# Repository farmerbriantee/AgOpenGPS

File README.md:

# AgOpenGPS - Guidance software

Ag Precision Mapping and Section Control Software

AgOpenGPS is 2 programs. AgIO is the communication hub to the outside world and AgOpenGPS is the 
application. You can run either and within each, you can run the other.

You only need to run AgOpenGPS if you are using the simulator.

The software reads NMEA strings for the purpose of recording and mapping position information 
for Agricultural use. Also it has up to 16 sections of Section Control that can have unique widths 
or up to 64 same width sections to control implements application of product preventing 
over-application.

Also ouputs Pure pursuit steer angles from reference line for AB line, AB Curve and Contour guidance. 
Auto Headland called UTurn on Curve and AB Line with loops for narrow equipment. 
Mapping as a background can also be added.

Included in this repository is an application, and source folders. 

See the PCB repo for PCB layouts, firmware for steering and rate control, machine control, GPS and simulator. 

## Installation

1. Download the [Most Stable AgOpenGPS Release](https://github.com/farmerbriantee/AgOpenGPS/releases)
2. Unzip or extract the contents to a folder (folder accessible by user not the root of C:\\)
Even on your desktop
3. Run AgOpenGPS.exe

## Links

- [AgOpenGPS Wiki](https://github.com/farmerbriantee/AgOpenGPS/wiki)
- [AgOpenGPS Forum](https://discourse.agopengps.com/)
- [PCB and Firmware Repository](https://github.com/AgHardware/Boards)
- [SK21 Rate Control Repository](https://github.com/AgHardware/Rate_Control)
- [AgHardware Wiki](https://github.com/AgHardware/Boards/wiki)

## License

If you distribute copies of such a program, whether
gratis or for a fee, you must pass on to the recipients the same
freedoms that you received.  You must make sure that they, too, receive
or can get the source code.  And you must show them these terms so they
know their rights as Outlined in the GPLv3 License.

THIS SOFTWARE IS PROVIDED BY THE COPYRIGHT HOLDERS AND CONTRIBUTORS "AS IS" AND ANY EXPRESS OR IMPLIED WARRANTIES, INCLUDING, BUT NOT LIMITED TO, THE IMPLIED WARRANTIES OF MERCHANTABILITY AND FITNESS FOR A PARTICULAR PURPOSE ARE DISCLAIMED.
IN NO EVENT SHALL <COPYRIGHT HOLDER> BE LIABLE FOR ANY DIRECT, INDIRECT, INCIDENTAL, SPECIAL, EXEMPLARY, OR CONSEQUENTIAL DAMAGES (INCLUDING, BUT NOT LIMITED TO, PROCUREMENT OF SUBSTITUTE GOODS OR SERVICES;
LOSS OF USE, DATA, OR PROFITS; OR BUSINESS INTERRUPTION) HOWEVER CAUSED AND ON ANY THEORY OF LIABILITY, WHETHER IN CONTRACT, STRICT LIABILITY, OR TORT (INCLUDING NEGLIGENCE OR OTHERWISE) ARISING IN ANY WAY OUT OF THE USE OF THIS SOFTWARE, EVEN IF ADVISED OF THE POSSIBILITY OF SUCH DAMAGE.

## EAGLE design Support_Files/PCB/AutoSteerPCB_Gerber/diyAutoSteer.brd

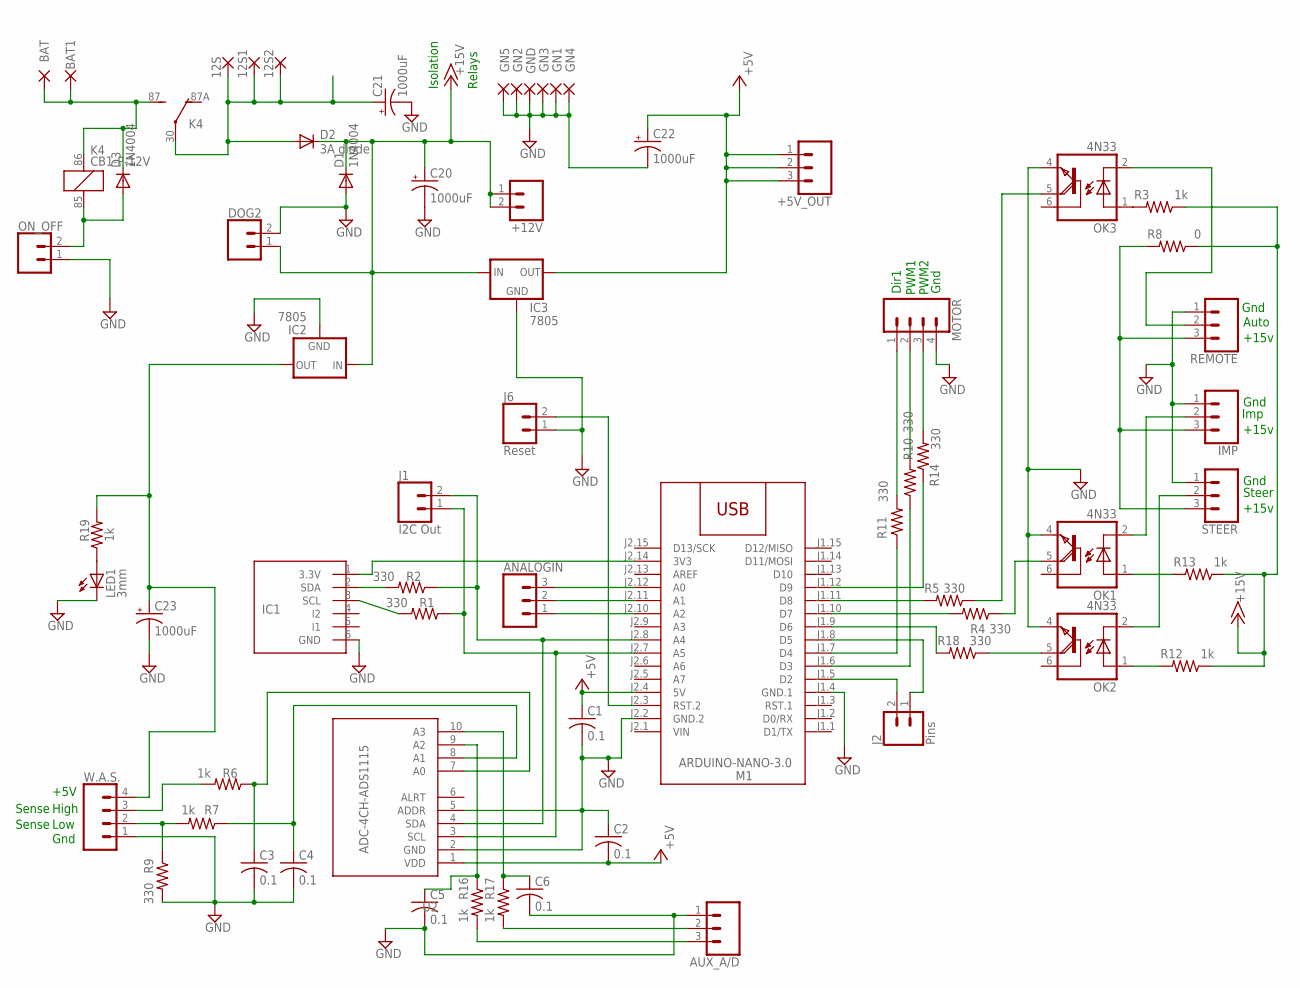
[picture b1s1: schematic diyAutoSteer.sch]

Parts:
12S, 12S1, 12S2: WIREPAD3,81/1,1; 3,81/1,1
+5V_OUT: CONN_03LONGPADS; 1X03_LONGPADS
+12V: CONN_02PTH3; 1X02_LONGPADS
ANALOGIN: CONN_03LONGPADS; 1X03_LONGPADS
AUX_A/D: CONN_03LONGPADS; 1X03_LONGPADS
BAT, BAT1: WIREPAD3,81/1,1; 3,81/1,1
C1, C2, C3, C4, C5, C6: 0.1; C025-025X050
C20, C21, C22, C23: 1000uF; E5-10,5
D1, D3: 1N4004; DO41-10
D2: 3A diode; DO27-15
DOG2: CONN_02PTH3; 1X02_LONGPADS
GN1, GN2, GN3, GN4, GN5: WIREPAD3,81/1,1; 3,81/1,1
GND: WIREPAD3,81/1,1; 3,81/1,1
IC1: MMA8452Q; BREAKOUT_6PIN
IC2, IC3: 7805; 78XXS
IMP: CONN_03LONGPADS; 1X03_LONGPADS
J1: I2C Out; 1X02_LONGPADS
J2: Pins; 1X02_LONGPADS
J6: Reset; 1X02_LONGPADS
K4: CB1-P-12V; CB1
LED1: 3mm; LED3MM
M1: ARDUINO-NANO-3.0
MOTOR: CONN_04LONGPADS; 1X04_LONGPADS
OK1, OK2, OK3: 4N33; DIL06
ON_OFF: CONN_02PTH3; 1X02_LONGPADS
R1, R2, R4, R5, R9, R10, R11, R14, R18: 330; 0309/12
R3, R6, R7, R12, R13, R16, R17, R19: 1k; 0309/12
R8: 0; 0309/12
REMOTE: CONN_03LONGPADS; 1X03_LONGPADS
STEER: CONN_03LONGPADS; 1X03_LONGPADS
U2: ADC-4CH-ADS1115
W.A.S.: CONN_04LONGPADS; 1X04_LONGPADS

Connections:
+5V: +5V_OUT.1, +5V_OUT.2, +5V_OUT.3, C1.1, C2.2, C22.+, IC3.OUT, M1.J2.4 (5V), U2.1 (VDD)
+15V: +12V.1, +12V.2, C20.+, D1.C, D2.C, DOG2.1, IC2.IN, IC3.IN, R3.1, R8.1, R12.1, R13.1
BATT: BAT.1, BAT1.1, D3.C, K4.86 (1), K4.87 (S)
GND: AUX_A/D.1, C1.2, C2.1, C3.2, C4.2, C5.2, C6.2, C20.-, C21.-, C22.-, C23.-, D1.A, DOG2.2, GN1.1, GN2.1, GN3.1, GN4.1, GN5.1, GND.1, IC1.6 (GND), IC2.GND, IC3.GND, IMP.1, J6.1, LED1.K (C), M1.J1.4 (GND.1), M1.J2.2 (GND.2), MOTOR.4, OK1.4 (E), OK2.4 (E), OK3.4 (E), ON_OFF.1, R9.2, REMOTE.1, STEER.1, U2.2 (GND), U2.5 (ADDR), W.A.S..1
unnamed: IC1.1 (3.3V), M1.J2.14 (3V3)
unnamed: R7.2, R9.1, W.A.S..2
unnamed: IMP.3, R8.2, REMOTE.3, STEER.3
unnamed: M1.J1.6 (D3), R10.1
unnamed: M1.J1.7 (D4), R11.1
unnamed: J2.2, M1.J1.5 (D2)
unnamed: J6.2, M1.J2.3 (RST.2)
unnamed: R6.2, W.A.S..3
unnamed: ANALOGIN.3, M1.J2.12 (A0)
unnamed: M1.J1.12 (D9), R14.1
unnamed: IC1.2 (SDA), R2.2
unnamed: IC1.3 (SCL), R1.2
unnamed: ANALOGIN.2, M1.J2.11 (A1)
unnamed: ANALOGIN.1, M1.J2.10 (A2)
unnamed: LED1.A, R19.1
unnamed: MOTOR.2, R10.2
unnamed: J2.1, M1.J1.8 (D5)
unnamed: MOTOR.1, R11.2
unnamed: C3.1, R6.1, U2.7 (A0)
unnamed: MOTOR.3, R14.2
unnamed: OK2.2 (C), STEER.2
unnamed: M1.J1.11 (D8), R5.2
unnamed: D3.A, K4.85 (2), ON_OFF.2
unnamed: OK2.1 (A), R12.2
unnamed: OK3.1 (A), R3.2
unnamed: M1.J1.10 (D7), R4.2
unnamed: OK3.2 (C), REMOTE.2
unnamed: IMP.2, OK1.2 (C)
unnamed: M1.J1.9 (D6), R18.2
unnamed: OK1.1 (A), R13.2
unnamed: OK3.5 (COL), R5.1
unnamed: C6.1, R17.1, U2.10 (A3)
unnamed: C5.1, R16.1, U2.9 (A2)
unnamed: OK1.5 (COL), R4.1
unnamed: AUX_A/D.2, R17.2
unnamed: OK2.5 (COL), R18.1
unnamed: C4.1, R7.1, U2.8 (A1)
unnamed: AUX_A/D.3, R16.2
SCL: J1.1, M1.J2.7 (A5), R1.1, U2.3 (SCL)
SDA: J1.2, M1.J2.8 (A4), R2.1, U2.4 (SDA)
SW_RAW: 12S.1, 12S1.1, 12S2.1, C21.+, D2.A, K4.30
V+WAS: C23.+, IC2.OUT, R19.2, W.A.S..4
VIN: M1.J2.1 (VIN)

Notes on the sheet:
Gnd
Low
High
+5V
PWM1
PWM2
Dir1
Steer
Imp
Sense
Auto
Isolation
Relays
+15v

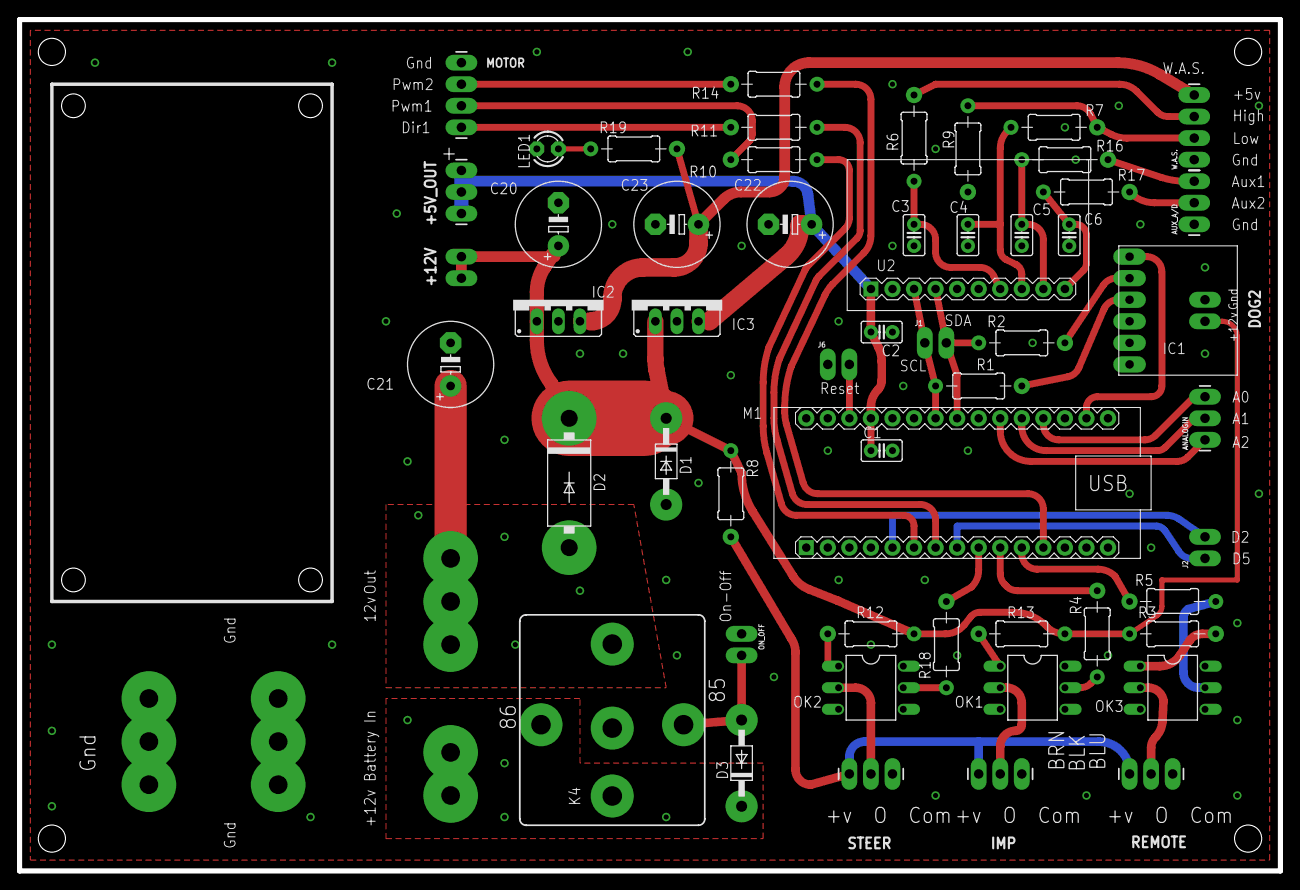
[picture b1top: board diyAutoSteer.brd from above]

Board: 2 copper layers, 148.6 x 100.3 mm, 66 parts (0 on the bottom side), 46 nets.

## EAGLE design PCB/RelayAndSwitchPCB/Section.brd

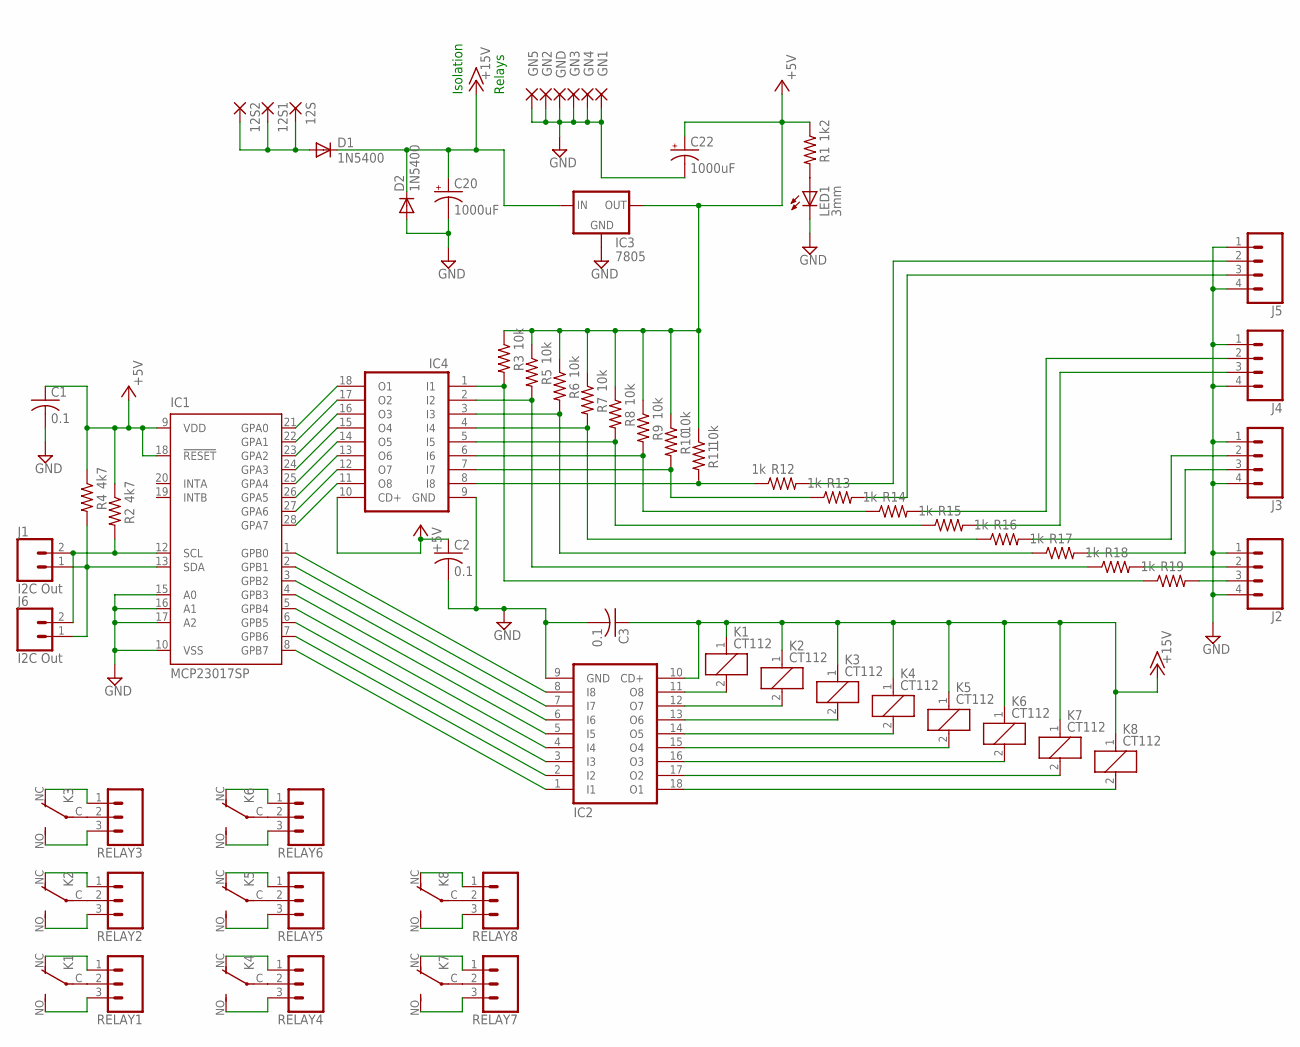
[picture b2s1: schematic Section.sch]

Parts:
12S, 12S1, 12S2: WIREPAD3,81/1,1; 3,81/1,1
C1, C2, C3: 0.1; C025-025X050
C20, C22: 1000uF; E5-10,5
D1, D2: 1N5400; DO201-15
GN1, GN2, GN3, GN4, GN5: WIREPAD3,81/1,1; 3,81/1,1
GND: WIREPAD3,81/1,1; 3,81/1,1
IC1: MCP23017SP; DIL28-3
IC2, IC4: ULN2803A; DIL18
IC3: 7805; 78XXS
J1, J6: I2C Out; 1X02_LONGPADS
J2, J3, J4, J5: CONN_04LONGPADS; 1X04_LONGPADS
K1, K2, K3, K4, K5, K6, K7, K8: CT112; CT-SLIM
LED1: 3mm; LED3MM
R1: 1k2; 0309/12
R2, R4: 4k7; 0309/12
R3, R5, R6, R7, R8, R9, R10, R11: 10k; 0309/12
R12, R13, R14, R15, R16, R17, R18, R19: 1k; 0309/12
RELAY1, RELAY2, RELAY3, RELAY4, RELAY5, RELAY6, RELAY7, RELAY8: CONN_03LONGPADS; 1X03_LONGPADS

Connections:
+5V: C1.1, C2.1, C22.+, IC1.9 (VDD), IC1.18 (!RESET), IC3.OUT, IC4.10 (CD+), R1.1, R2.1, R3.1, R4.1, R5.1, R6.1, R7.1, R8.1, R9.1, R10.1, R11.1
+12SW: 12S.1, 12S1.1, 12S2.1, D1.A
+15V: C3.1, C20.+, D1.C, D2.C, IC2.10 (CD+), IC3.IN, K1.1, K2.1, K3.1, K4.1, K5.1, K6.1, K7.1, K8.1
GND: C1.2, C2.2, C3.2, C20.-, C22.-, D2.A, GN1.1, GN2.1, GN3.1, GN4.1, GN5.1, GND.1, IC1.10 (VSS), IC1.15 (A0), IC1.16 (A1), IC1.17 (A2), IC2.9 (GND), IC3.GND, IC4.9 (GND), J2.1, J2.4, J3.1, J3.4, J4.1, J4.4, J5.1, J5.4, LED1.K (C)
unnamed: IC2.11 (O8), K1.2
unnamed: IC1.1 (GPB0), IC2.8 (I8)
unnamed: IC1.2 (GPB1), IC2.7 (I7)
unnamed: IC1.3 (GPB2), IC2.6 (I6)
unnamed: IC1.4 (GPB3), IC2.5 (I5)
unnamed: IC1.5 (GPB4), IC2.4 (I4)
unnamed: IC1.6 (GPB5), IC2.3 (I3)
unnamed: IC1.7 (GPB6), IC2.2 (I2)
unnamed: IC1.8 (GPB7), IC2.1 (I1)
unnamed: IC2.12 (O7), K2.2
unnamed: IC2.13 (O6), K3.2
unnamed: IC2.14 (O5), K4.2
unnamed: IC2.15 (O4), K5.2
unnamed: IC2.16 (O3), K6.2
unnamed: IC2.17 (O2), K7.2
unnamed: IC2.18 (O1), K8.2
unnamed: IC1.21 (GPA0), IC4.18 (O1)
unnamed: IC1.22 (GPA1), IC4.17 (O2)
unnamed: K1.C, RELAY1.2
unnamed: K2.C, RELAY2.2
unnamed: K3.C, RELAY3.2
unnamed: K5.C, RELAY5.2
unnamed: K4.C, RELAY4.2
unnamed: K6.C, RELAY6.2
unnamed: K7.C, RELAY7.2
unnamed: IC1.23 (GPA2), IC4.16 (O3)
unnamed: K8.C, RELAY8.2
unnamed: IC1.24 (GPA3), IC4.15 (O4)
unnamed: K1.NC (O), RELAY1.1
unnamed: K1.NO (S), RELAY1.3
unnamed: K2.NO (S), RELAY2.3
unnamed: K2.NC (O), RELAY2.1
unnamed: K3.NO (S), RELAY3.3
unnamed: IC1.25 (GPA4), IC4.14 (O5)
unnamed: K3.NC (O), RELAY3.1
unnamed: K6.NC (O), RELAY6.1
unnamed: K6.NO (S), RELAY6.3
unnamed: K5.NC (O), RELAY5.1
unnamed: K5.NO (S), RELAY5.3
unnamed: K4.NC (O), RELAY4.1
unnamed: K4.NO (S), RELAY4.3
unnamed: K7.NO (S), RELAY7.3
unnamed: K7.NC (O), RELAY7.1
unnamed: K8.NO (S), RELAY8.3
unnamed: K8.NC (O), RELAY8.1
unnamed: LED1.A, R1.2
unnamed: IC1.26 (GPA5), IC4.13 (O6)
unnamed: IC1.27 (GPA6), IC4.12 (O7)
unnamed: IC1.28 (GPA7), IC4.11 (O8)
unnamed: IC4.8 (I8), R11.2, R12.1
unnamed: IC4.7 (I7), R10.2, R13.1
unnamed: IC4.6 (I6), R9.2, R14.1
unnamed: IC4.5 (I5), R8.2, R15.1
unnamed: IC4.4 (I4), R7.2, R16.1
unnamed: IC4.3 (I3), R6.2, R17.1
unnamed: IC4.2 (I2), R5.2, R18.1
unnamed: IC4.1 (I1), R3.2, R19.1
unnamed: J2.3, R19.2
unnamed: J2.2, R18.2
unnamed: J3.3, R17.2
unnamed: J3.2, R16.2
unnamed: J4.3, R15.2
unnamed: J4.2, R14.2
unnamed: J5.3, R13.2
unnamed: J5.2, R12.2
SCL: IC1.12 (SCL), J1.2, J6.2, R2.2
SDA: IC1.13 (SDA), J1.1, J6.1, R4.2

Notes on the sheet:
Isolation
Relays

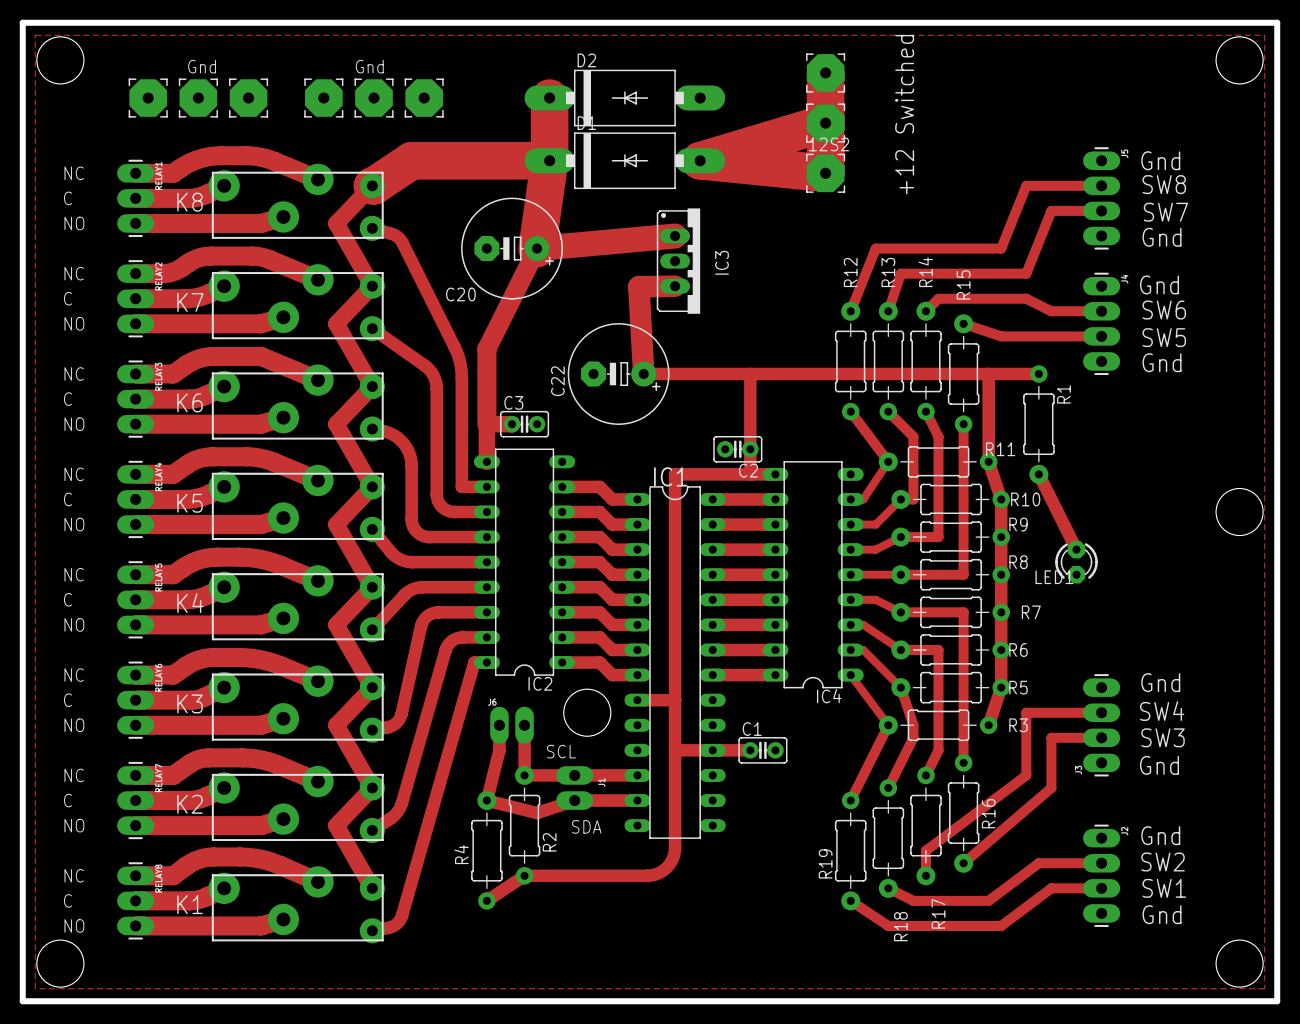
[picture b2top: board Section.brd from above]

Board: 2 copper layers, 127.0 x 99.1 mm, 62 parts (0 on the bottom side), 71 nets.

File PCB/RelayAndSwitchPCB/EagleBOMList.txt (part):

Partlist exported from C:/Users/Grizs/Documents/eagle7/Section/Section.sch at 2019-03-19 4:59 PM

Part   Value           Device          Package       Description                                                                                                  
12S    WIREPAD3,81/1,1 WIREPAD3,81/1,1 3,81/1,1      Wire PAD connect wire on PCB                                                                                                                                           
12S1   WIREPAD3,81/1,1 WIREPAD3,81/1,1 3,81/1,1      Wire PAD connect wire on PCB                                                                                                                                           
12S2   WIREPAD3,81/1,1 WIREPAD3,81/1,1 3,81/1,1      Wire PAD connect wire on PCB                                                                                                                                           
C1     0.1             C-US025-025X050 C025-025X050  CAPACITOR, American symbol                                                                                                                                             
C2     0.1             C-US025-025X050 C025-025X050  CAPACITOR, American symbol                                                                                                                                             
C3     0.1             C-US025-025X050 C025-025X050  CAPACITOR, American symbol                                                                                                                                             
C20    1000uF          CPOL-USE5-10.5  E5-10,5       POLARIZED CAPACITOR, American symbol                                                                                                                                   
C22    1000uF          CPOL-USE5-10.5  E5-10,5       POLARIZED CAPACITOR, American symbol                                                                                                                                   
D1     1N5400          1N5400          DO201-15      DIODE                                                                                                                                                                  
D2     1N5400          1N5400          DO201-15      DIODE                                                                                                                                                                  
GN1    WIREPAD3,81/1,1 WIREPAD3,81/1,1 3,81/1,1      Wire PAD connect wire on PCB                                                                                                                                           
GN2    WIREPAD3,81/1,1 WIREPAD3,81/1,1 3,81/1,1      Wire PAD connect wire on PCB                                                                                                                                           
GN3    WIREPAD3,81/1,1 WIREPAD3,81/1,1 3,81/1,1      Wire PAD connect wire on PCB                                                                                                                                           
GN4    WIREPAD3,81/1,1 WIREPAD3,81/1,1 3,81/1,1      Wire PAD connect wire on PCB                                                                                                                                           
GN5    WIREPAD3,81/1,1 WIREPAD3,81/1,1 3,81/1,1      Wire PAD connect wire on PCB                                                                                                                                           
GND    WIREPAD3,81/1,1 WIREPAD3,81/1,1 3,81/1,1      Wire PAD connect wire on PCB                                                                                                                                           
IC1    MCP23017SP      MCP23017SP      DIL28-3       http://ww1.microchip.com/downloads/en/DeviceDoc/21952a.pdf                
IC2                    ULN2803A        DIL18         DRIVER ARRAY                                                                                                                                                           
IC3    7805            78XXS           78XXS         VOLTAGE REGULATOR                                                                                                                                                      
IC4                    ULN2803A        DIL18         DRIVER ARRAY                                                                                                                                                           
J1     I2C Out         CONN_02PTH3     1X02_LONGPADS Multi connection point. 
J2                     CONN_04LONGPADS 1X04_LONGPADS Multi connection point. 
J3                     CONN_04LONGPADS 1X04_LONGPADS Multi connection point. 
J4                     CONN_04LONGPADS 1X04_LONGPADS Multi connection point. 
J5                     CONN_04LONGPADS 1X04_LONGPADS Multi connection point. 
J6     I2C Out         CONN_02PTH3     1X02_LONGPADS Multi connection point. 
K1     CT112           CT112           CT-SLIM       ULTRA SMALL AUTOMOTIVE RELAY 
K2     CT112           CT112           CT-SLIM       ULTRA SMALL AUTOMOTIVE RELAY              
K3     CT112           CT112           CT-SLIM       ULTRA SMALL AUTOMOTIVE RELAY        
K4     CT112           CT112           CT-SLIM       ULTRA SMALL AUTOMOTIVE RELAY 
K5     CT112           CT112           CT-SLIM       ULTRA SMALL AUTOMOTIVE RELAY 
K6     CT112           CT112           CT-SLIM       ULTRA SMALL AUTOMOTIVE RELAY 
K7     CT112           CT112           CT-SLIM       ULTRA SMALL AUTOMOTIVE RELAY 
K8     CT112           CT112           CT-SLIM       ULTRA SMALL AUTOMOTIVE RELAY 
LED1   3mm             LED3MM          LED3MM        LED                                                                                                                                                                    
R1     1k2             R-US_0309/12    0309/12       RESISTOR, American symbol                                                                                                                                              
R2     4k7             R-US_0309/12    0309/12       RESISTOR, American symbol                                                                                                                                              
R3     10k             R-US_0309/12    0309/12       RESISTOR, American symbol                                                                                                                                              
R4     4k7             R-US_0309/12    0309/12       RESISTOR, American symbol                                                                                                                                              
R5     10k             R-US_0309/12    0309/12       RESISTOR, American symbol                                                                                                                                              
R6     10k             R-US_0309/12    0309/12       RESISTOR, American symbol                                                                                                                                              
R7     10k             R-US_0309/12    0309/12       RESISTOR, American symbol                                                                                                                                              
R8     10k             R-US_0309/12    0309/12       RESISTOR, American symbol                                                                                                                                              
R9     10k             R-US_0309/12    0309/12       RESISTOR, American symbol                                                                                                                                              
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
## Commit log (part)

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2024-02-16 Sound for going to fast
2024-02-16 line to -1
2024-02-17 Extend Tram lines
2024-02-19 Albvig uturn code
2024-02-19 uturn alarms & reduced points
2024-02-19 AgIO minor changes for VA
2024-02-21 Close class
2024-02-21 firstClosePoint
2024-02-21 heading limits
2024-02-21 Segments same code
2024-02-21 formatting
2024-02-21 when more then one segment
2024-02-21 edge case when index is turnCount
2024-02-23 Fix 239 section order
2024-02-23 229 fix
2024-02-23 Fix 229
    4
2024-02-23 create out curve
2024-02-24 Fill in gap
2024-02-24 Add norwegian
2024-02-25 uturn byte fix
2024-02-25 uturn works curve
2024-02-25 Remove next/prev line delay
2024-02-25 Final changes for now on uturn
2024-02-26 separate ohmega and wide turn
2024-02-26 stable ab
2024-02-28 Cleanup
2024-03-01 Albin merge
2024-03-01 uturn mode on main ogl
2024-03-01 UTurnStyle saving from OGL
2024-03-04 add lop sided turns for trailed tbt
2024-03-04 gfx fixes
2024-03-06 Fix nudge and Skips text
2024-03-07 Add nudge to bottom panel
2024-03-08 Using Path.Combine() to build file paths. Makes paths OS independent. Should now run on Linux using Mono.
2024-03-09 remove help
2024-03-09 add exit to steer
2024-03-10 event for bing btn
2024-03-13 elevation file changes and setting
2024-03-13 sim adjusts elevation
2024-03-21 Little fixes
2024-03-22 section no sound, remote switches, uturn
2024-03-24 average XTE and font size
2024-03-26 dual reverse, section color, flag to ant
2024-03-26 remove "If Wrong direction"
2024-03-29 longer track menu timeout
2024-03-30 Revert "Merge pull request #382 from affeltranger/master"
    This reverts commit abbeda3338ee68732b735a208e20b26b7d447113, reversing
    changes made to 362d61f1fc5e28778a3a40f68136b2cd23194713.
2024-03-30 Revert "Merge pull request #383 from refactorau/spelling"
    This reverts commit 362d61f1fc5e28778a3a40f68136b2cd23194713, reversing
    changes made to c3f1d21b4d851390ced69d539b569ae1589e61fb.
2024-03-30 +semver: minor v6.1.0
2024-03-30 +semver: minor v6.1
2024-04-02 Elevation log image
2024-04-02 no gps fix
2024-04-03 Linux Loopback Names
2024-04-03 tram hidden remove touch detect
2024-04-04 no uturn for stanley
2024-04-04 extend curve +4 on each end
2024-04-05 stanley ab line from piv to steer
2024-04-05 fix stanley ab
2024-04-05 bnd tool start icon
2024-04-06 uturn fixes
2024-04-07 Pure Stan on Flag btn
2024-04-07 look ahead to 7 secs
2024-04-08 Add Chinese
2024-04-08 +semver: minor v6.2
2024-04-09 fix from existing
2024-04-09 Fix cancel on field menu
2024-04-12 xte fix, cancal on field menu
2024-04-14 Grid window, grid tool width
2024-04-15 auto trak to wider angle
2024-04-15 Grid and autoTrak
2024-04-15 skip line text update
2024-04-16 Fix autosnap
2024-04-16 remove minradius
2024-04-16 update radius images
2024-04-17 Help to youtube
2024-04-17 Boundary tool Gui
2024-04-19 map gui clean
2024-04-19 gps info button focus
2024-04-21 grid to zero
2024-04-22 point Add bnd tool
2024-04-23 Set integral default to 0
2024-04-24 roll corrected position
2024-04-26 Ping Timer
2024-04-27 change ping to advanced view
2024-04-27 record path name
2024-04-29 add skytraq 035
2024-04-29 pan in bnd tool v63
2024-04-29 Revert "move steer setting to steer form"
    This reverts commit 3ba914af24688727ad59975dbd9ea983188d0f1a.
2024-04-29 Fix config, brightness, AgIO header
2024-04-29 form steer fix
2024-05-02 Antenna Offset btns
2024-05-02 North 2D btn
2024-05-06 Fix auto remote button - remove setting
2024-05-06 v6.3.1
2024-05-08 Decimal zones
2024-05-09 take into account the adjustment of the light bar for use without autoguiding, particularly on quad
2024-05-09 Fix AV display, Default width Zone to 1 decimal
2024-05-20 cm Per Pixel added back in
2024-05-20 Fix cm per pixel
2024-05-21 Is on screen
2024-05-23 Kiosk mode added
2024-05-24 v 6.3.2
2024-05-28 no build line if same line
2024-05-29 async Task for bnd curve
2024-05-29 curve async ready flag
2024-05-30 button and section sizing
2024-05-30 Revert "button and section sizing"
    This reverts commit 1be1224ee8d6f53cac428827aa6c21027b7e4422.
2024-05-30 Revert "curve async ready flag"
    This reverts commit 8a9a179df639f0d79706bcd348b3540e82fa04c7.
2024-05-30 Revert "async Task for bnd curve"
    This reverts commit fd5f4b86ae67e56a7d1ec80fd3e43169c0486953.
2024-05-31 section sizes, Tasj bnd curve
2024-07-06 Add direction arrows
2024-07-12 Add Portugese
2024-08-08 Fix AgIO startup crash on corrupt user.config in %APPDATA%
2024-10-03 Update gStr.de.resx
    fix translation issue for DE: current->aktuell not strom
2024-10-12 fix pivot guidance offset problem
2024-10-16 limit section entry, fusion to 95%
2024-10-16 first implementation of searching for unworked lanes at YouTurn
2024-10-17 changed check for ab or curve mode
2024-10-19 remove unessesay curve.lastHowManyPathsAway = 98888 and curve.lastSecond = 0 because it already forces a new line when isCurveValid = false
2024-10-20 curve creation to async task
2024-10-20 CYouTurn Cleanup instead of changing guidancelookpos change howManyPathsAway nudgeDistance cleanup
2024-10-20 track mode to enum
2024-10-20 didnt notice because it was changed to string
2024-10-25 Don't lower if backing up
2024-10-26 adjust logic for markAsWorkedLine to work for manual and auto Section Master
2024-10-28 Update GUI.Designer.cs to load settings for YouTurn SkipWidth
2024-10-28 compiled Version
2024-10-29 clean code
2024-10-29 bugfix
2024-10-30 refactoring
2024-11-09 Fix AB Curve numbering
2024-11-09 Revert "Fix AB Curve numbering"
    This reverts commit 262729b6254e0e08de1a2014b96d8e8b7dcdedff.
2024-11-09 Agio Appdata recovery
2024-11-15 shutdown form changes
2024-11-15 Remove 3 and shorten code
2024-11-16 Fix shutdown exit cancel
2024-11-16 fixed DrawCurveNew and added manual add new point to curve
2024-11-16 ignore to ok
2024-11-17 B to OK64 for curve
2024-11-17 Curve Forms to ok
2024-11-19 Add All Setting View
2024-11-19 Fix snap settings icon
2024-11-19 Update gStr.fr.resx
    replace "lignes de grandes largeurs" by "jalons" in french
2024-11-19 group settings
2024-11-19 Auto Agio Off
2024-11-19 Clipboard button
2024-11-20 exit/shutdown defaults
2024-11-20 remove shutdown AgIO Fat new curve
2024-11-21 Power Loss Shutdown Feature
2024-11-21 Clean up menus for setting dupes
2024-11-21 Fix culture on menu
2024-11-21 room for power inicator
2024-11-21 cancel save or not when power returns
2024-11-22 fix screenshot
2024-11-25 Remove rate and shapefile unused code
2024-11-25 update gitignore for _v64
2024-11-25 Add hardware message
2024-11-25 cbox for hardwaremessage enable
2024-11-26 Auto Run GPS_Out, move X and slide panel btns
2024-11-26 Resize buttons
2024-11-26 simplify ethernet form and ethernet on off
2024-11-26 remove test code from AgIO start
2024-11-27 Remove random letters from Bound Player
2024-11-27 Revert "Remove random letters from Bound Player"
    This reverts commit 27d464acfebc2a41a2f77319d13e76a19b9b8133.
2024-11-27 simplify reset youturn
2024-11-27 Arrange events in order
2024-11-28 jumpFix for Fix put after roll and offset correction
2024-11-28 update jumpFix for Fix heading group
2024-11-28 Put jump label in left panel
2024-11-28 kill autosteer re enable and setting
2024-11-28 height of AgIO and AllSettings Timer refresh
2024-11-30 NTRIP Source table btn disable till return from attempting
2024-12-01 jump fix not storing correct fix history
2024-12-02 set min to go as high as 200
2024-12-03 Deadzone added
2024-12-03 noupdate pgn when in dead zone
2024-12-04 MAke tracks menu vertical
2024-12-04 Status to zero when in dead zone
2024-12-04 gui fixes
2024-12-05 Step distance for distance gauge
2024-12-05 Move language files to culture directory. Huge change
2024-12-05 Black border
2024-12-06 ModSim added to AgIO
2024-12-06 ModSim Menu Image
2024-12-07 Boundary confirmation title
2024-12-07 Make forms same color theme, boring grey
2024-12-07 Remove end of curve notification from curve class
2024-12-09 Error bar line
2024-12-09 Remove solution configuration 'All'
2024-12-09 Remove unused source files
2024-12-09 steer error graph dev
2024-12-09 Local search instead of global when following a curve
    The previous implementation led the vehicle to sometimes pick a wrong part of a curve when the curve was intersecting itself (AB-curve) or there were more than one parallel lines near to each other (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
    This changes the curve-following algorithm to use a search for "local" nearest point instead of "global" (= taking all the points on the curve into account) when already following the curve.
    Look ahead-distance is used when searching the nearest "local" point to prevent problems in tight hairpins caused by the search sticking
2024-12-10 steer error bar still changes
2024-12-10 2 triangle bar
2024-12-10 double arrows
2024-12-10 Fix tram button position and tap
2024-12-11 pudh graphics final steer bar, add old light bar back
2024-12-11 Reduce arrow on steer bar
2024-12-11 update French Tramline translation
2024-12-11 GNSS-Stylist find nearest Global curve point
2024-12-11 hyd lift enable
2024-12-11 Lookahead set to 20cm and 1 sec long when not in AS
2024-12-11 PP response and grafix.
2024-12-11 Speed factor is 1.4 hard coded
2024-12-11 Combine Deadzone and bar guis in formsteer
2024-12-12 Align text for Steer and XTE bars
2024-12-12 Smallify arrows on autosteer
2024-12-12 prevent window from being minimized during critical operation
2024-12-12 Align grid to AB
2024-12-13 Direction triangle sizing
2024-12-13 License to program folder
2024-12-13 Add ramped loookahead
2024-12-13 update license date
2024-12-14 Ramped lookahead from 40 to 10 cm
2024-12-14 Migrate to PackageReference
2024-12-14 Use NuGet package of WebCameraControl
2024-12-14 Use NuGet package of Control.Draggable
2024-12-14 Use NuGet package of OpenTK
2024-12-14 Add Keypad as ProjectReference
2024-12-14 Shading for section lookahead, follow up patch at night
2024-12-14 Enter num of guidelines
2024-12-15 Steer Events log
2024-12-16 system event tags, skips to 9
2024-12-16 Event viewer update
2024-12-16 Max 0.5 mbyte events log file
2024-12-16 20 second RTK Kill autosteer delay
2024-12-16 Add delay to deadzone
2024-12-17 Gradient Backcolor for XTE
2024-12-17 Turn offButton Features in menus to be simpler default
2024-12-17 Section border lines, guides control on Tools
2024-12-17 Small Timed message box
2024-12-17 Change tram colors
2024-12-17 v6.4.1
2024-12-17 Save Delay to settings
2024-12-17 sim steer angle x 0.75
2024-12-17 Upgrade settings from previous version
2024-12-17 Remove pull old settings
2024-12-18 Add Nozzle from Drive
2024-12-18 dead zone delay to 5
2024-12-18 Fix wrong bracketing on Load FormGPS
2024-12-18 fix bracket in formGPS load
2024-12-18 Add a contributing section to the README
2024-12-18 Restructure main README
2024-12-18 balck background on fence bound and guide
2024-12-18 try catch for drawing flags
2024-12-18 RTK fix alarm and AS Kill to immediate.
2024-12-18 Catch up to bug, highlights, Alpha, killsteer
2024-12-18 fix settings odd changes
2024-12-18 add line bkgrnds
2024-12-18 remove v65 folder
2024-12-18 pre delete app.config
2024-12-18 Antialias enabled
2024-12-18 widen Nozz panel and move gps data, field data
2024-12-19 move pan to left center
2024-12-19 Added Elevation to the Flag Form
    Elevation added to flag window, flag.txt and KMLs
2024-12-19 Profile Saving and creating
2024-12-19 form bnd player changes
2024-12-20 Form Steer nerd, Logs Directory
2024-12-20 System Event writer messages
2024-12-21 Move event viewer
2024-12-21 set to v6.4.5
2024-12-21 Left Right Tool Pivot Bnd creation
2024-12-21 widen direction arrows
2024-12-21 Add Log Viewer
2024-12-21 Setting for bnd draw pivot
2024-12-21 Update view all settings

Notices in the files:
parts and their libraries:
SparkFun-Connectors: Licensing: Creative Commons ShareAlike 4.0 International - https://creativecommons.org/licenses/by-sa/4.0
diy-modules: Released under the Creative Commons Attribution 4.0 International License: http://creativecommons.org/licenses/by/4.0
